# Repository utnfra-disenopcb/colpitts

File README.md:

# Diseño de PCB de oscilador Colpitts de frecuencia variable (80MHz a 100MHz)

## Enunciado
El proyecto consiste en el desarrollo de un oscilador de frecuencia variable, de 80MHz a 100MHz, a través de un capacitor variable (trimmer). El diseño incluye un control automático de amplitud de forma tal de mantener la tensión de salida estable en 1V aproximadamente, sobre una carga de 50Ω y con una THD menor al 5%. Para su construcción se emplea un oscilador tipo Colpitts con configuración base a masa.

## Referencias de diseño

**Tecnologías**
- Mayer (Tecnología 8 mils)
- Pistas: 1.5; 1; 0.75; 0.5; 0.25; 0.20 [mm]
- Vías: 0.8 - Agujero: 0.4 [mm]
- Márgen: 0.25 mm
- Pista más delgada: 0.2 mm
- Dist. a borde: 0.3 mm

**Stack-up**
- FR4 1.6 mm Dual layer
- Componentes en capa superior
- Máscara anti-soldante: Azul
- Sin requerimientos especiales
- Terminación: HASL c/Pb
- Espesor de Cu: 1oz

## Historial de versiones

**Versión 1.0**
- Primera versión.

## Mejoras pendientes v1.1
- Mejora 1
- Mejora 2
- Mejora 3

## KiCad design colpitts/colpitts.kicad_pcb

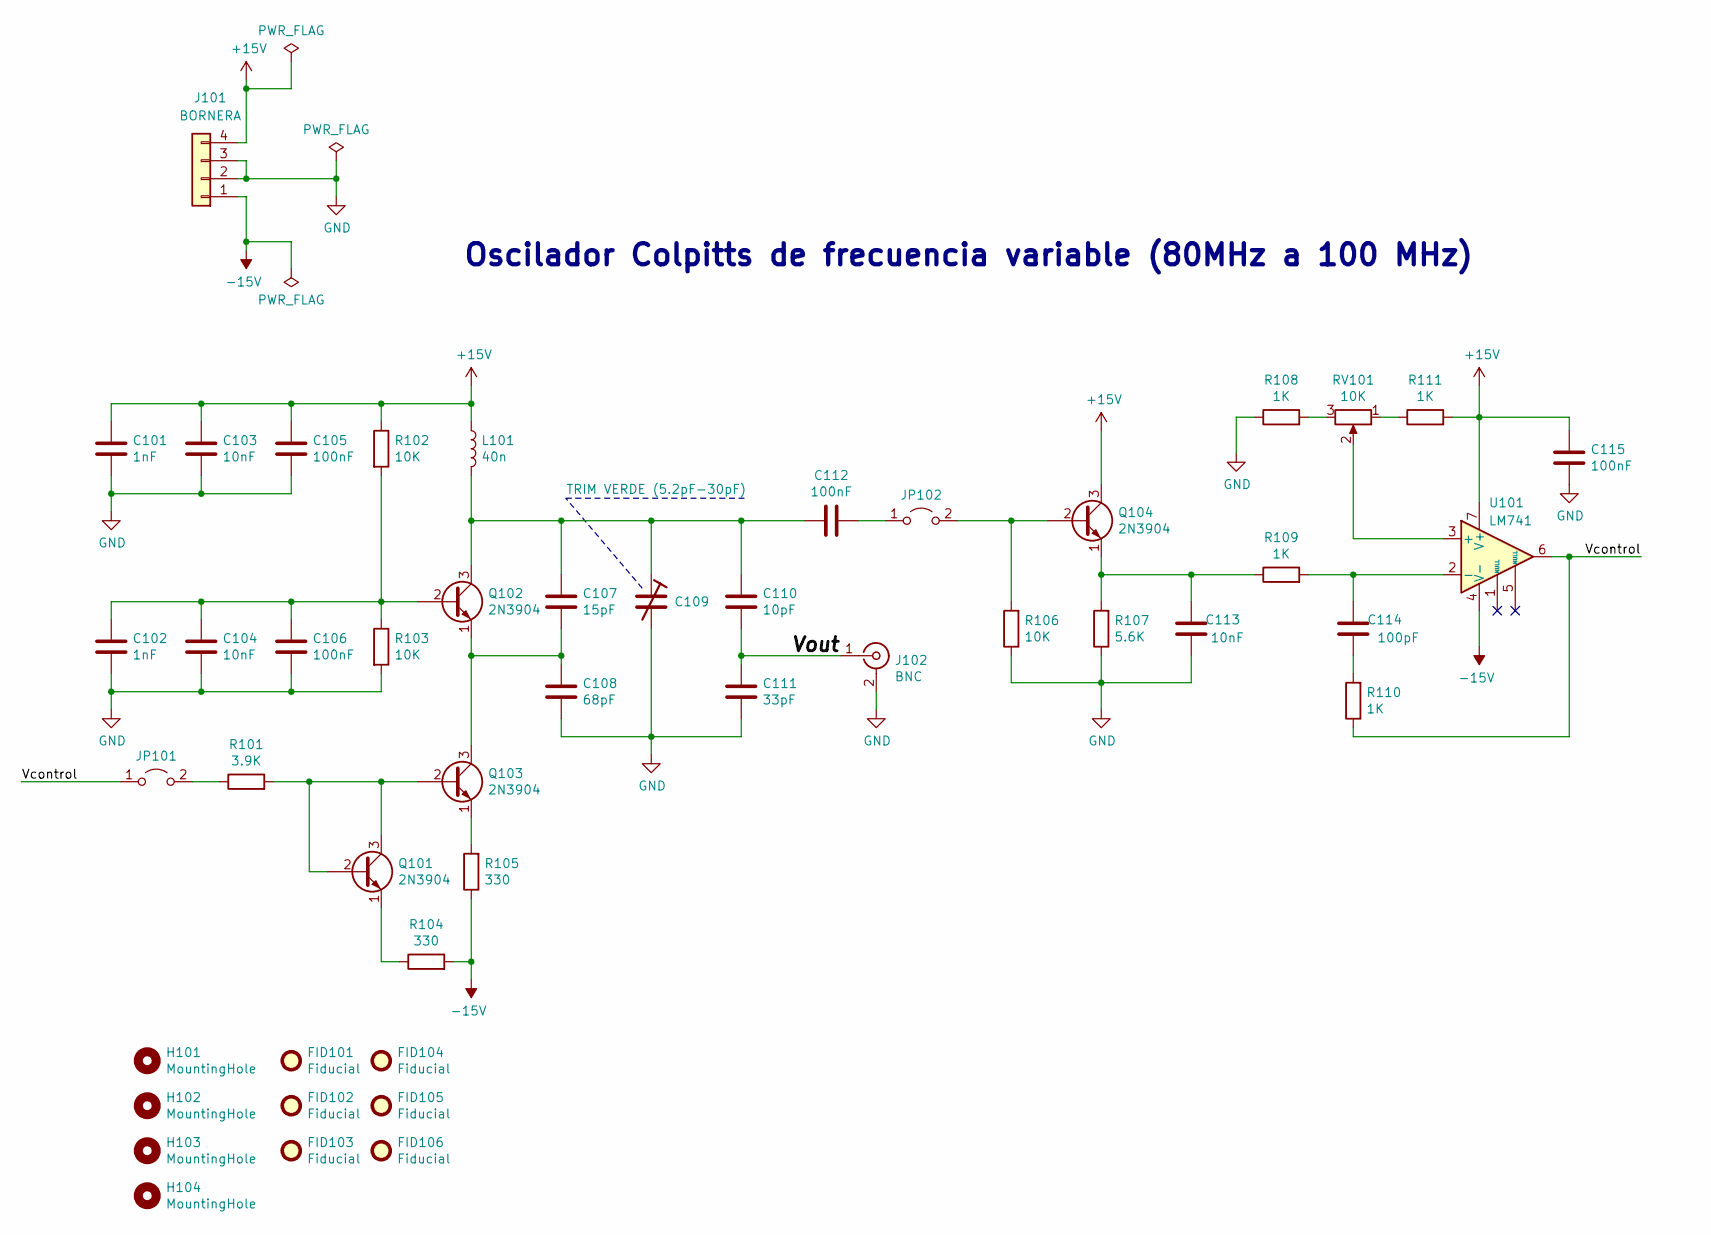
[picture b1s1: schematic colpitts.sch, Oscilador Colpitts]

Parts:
C101, C102: 1nF; C_0805_2012Metric_Pad1.15x1.40mm_HandSolder
C103, C104, C113: 10nF; C_0805_2012Metric_Pad1.15x1.40mm_HandSolder
C105, C106, C112, C115: 100nF; C_0805_2012Metric_Pad1.15x1.40mm_HandSolder
C107: 15pF; C_0805_2012Metric_Pad1.15x1.40mm_HandSolder
C108: 68pF; C_0805_2012Metric_Pad1.15x1.40mm_HandSolder
C109: TRIM VERDE (5.2pF-30pF); Trimmer_Capacitor_Verde; DigiKey PN 490-1960-ND
C110: 10pF; C_0805_2012Metric_Pad1.15x1.40mm_HandSolder
C111: 33pF; C_0805_2012Metric_Pad1.15x1.40mm_HandSolder
C114: 100pF; C_0805_2012Metric_Pad1.15x1.40mm_HandSolder
FID101, FID102, FID103, FID104, FID105, FID106: Fiducial; Fiducial_1mm_Mask2mm
H101, H102, H103, H104: MountingHole; MountingHole_3.2mm_M3_Pad_Via
J101: BORNERA; TerminalBlock_1x04_P5.00mm; DigiKey PN 277-1579-ND
J102: BNC; BNC_Conn_Horizontal; DigiKey PN A32244-ND
JP101, JP102: Jumper_2_Open; PinHeader_1x02_P2.54mm_Vertical
L101: 40n; L_Axial_L5.3mm_D2.2mm_P10.16mm_Horizontal_Vishay_IM-1
Q101, Q102, Q103, Q104: 2N3904; TO-92_Inline; DigiKey PN 2N3904FS-ND
R101: 3.9K; R_0805_2012Metric_Pad1.15x1.40mm_HandSolder
R102, R103, R106: 10K; R_0805_2012Metric_Pad1.15x1.40mm_HandSolder
R104, R105: 330; R_0805_2012Metric_Pad1.15x1.40mm_HandSolder
R107: 5.6K; R_0805_2012Metric_Pad1.15x1.40mm_HandSolder
R108, R109, R110, R111: 1K; R_0805_2012Metric_Pad1.15x1.40mm_HandSolder
RV101: 10K; Preset_Multivuelta
U101: LM741; DIP-8_W10.16mm; DigiKey PN LM741CNNS/NOPB-ND

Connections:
+15V: C101.1, C103.1, C105.1, C115.1, J101.4, L101.1, Q104.3 (C), R102.1, R111.2, U101.7 (V+)
-15V: J101.1, R104.2, R105.1, U101.4 (V-)
/Vcontrol: JP101.1 (A), R110.1, U101.6
/Vout: C110.2, C111.1, J102.1 (In)
GND: C101.2, C102.2, C103.2, C104.2, C105.2, C106.2, C108.2, C109.2, C111.2, C113.1, C115.2, J101.2, J101.3, J102.2 (Ext), R103.2, R106.1, R107.1, R108.1
unnamed: C102.1, C104.1, C106.1, Q102.2 (B), R102.2, R103.1
unnamed: C107.1, C109.1, C110.1, C112.2, L101.2, Q102.3 (C)
unnamed: C107.2, C108.1, Q102.1 (E), Q103.3 (C)
unnamed: C112.1, JP102.1 (A)
unnamed: C113.2, Q104.1 (E), R107.2, R109.1
unnamed: C114.1, R110.2
unnamed: C114.2, R109.2, U101.2 (-)
unnamed: JP101.2 (B), R101.1
unnamed: JP102.2 (B), Q104.2 (B), R106.2
unnamed: Q101.1 (E), R104.1
unnamed: Q101.2 (B), Q101.3 (C), Q103.2 (B), R101.2
unnamed: Q103.1 (E), R105.2
unnamed: R108.2, RV101.3
unnamed: R111.1, RV101.1
unnamed: RV101.2, U101.3 (+)

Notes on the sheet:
Oscilador Colpitts de frecuencia variable (80MHz a 100 MHz)

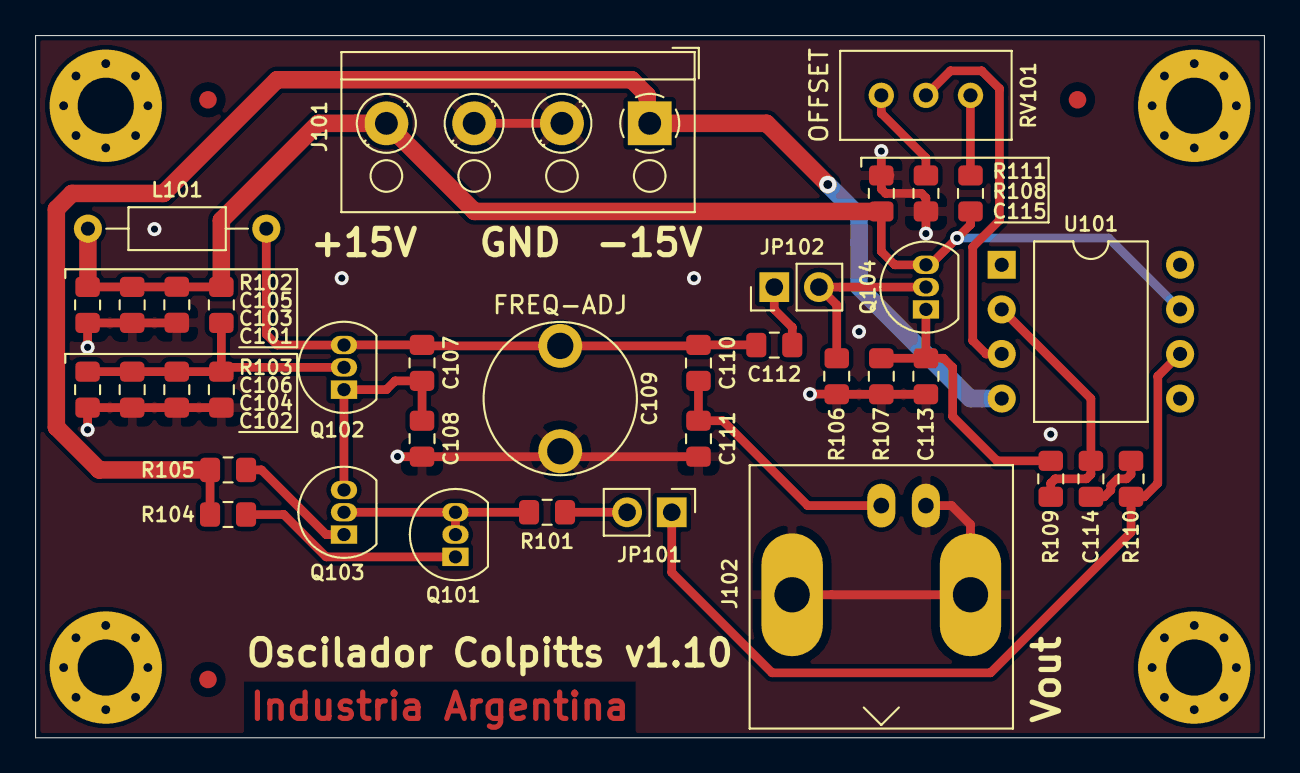
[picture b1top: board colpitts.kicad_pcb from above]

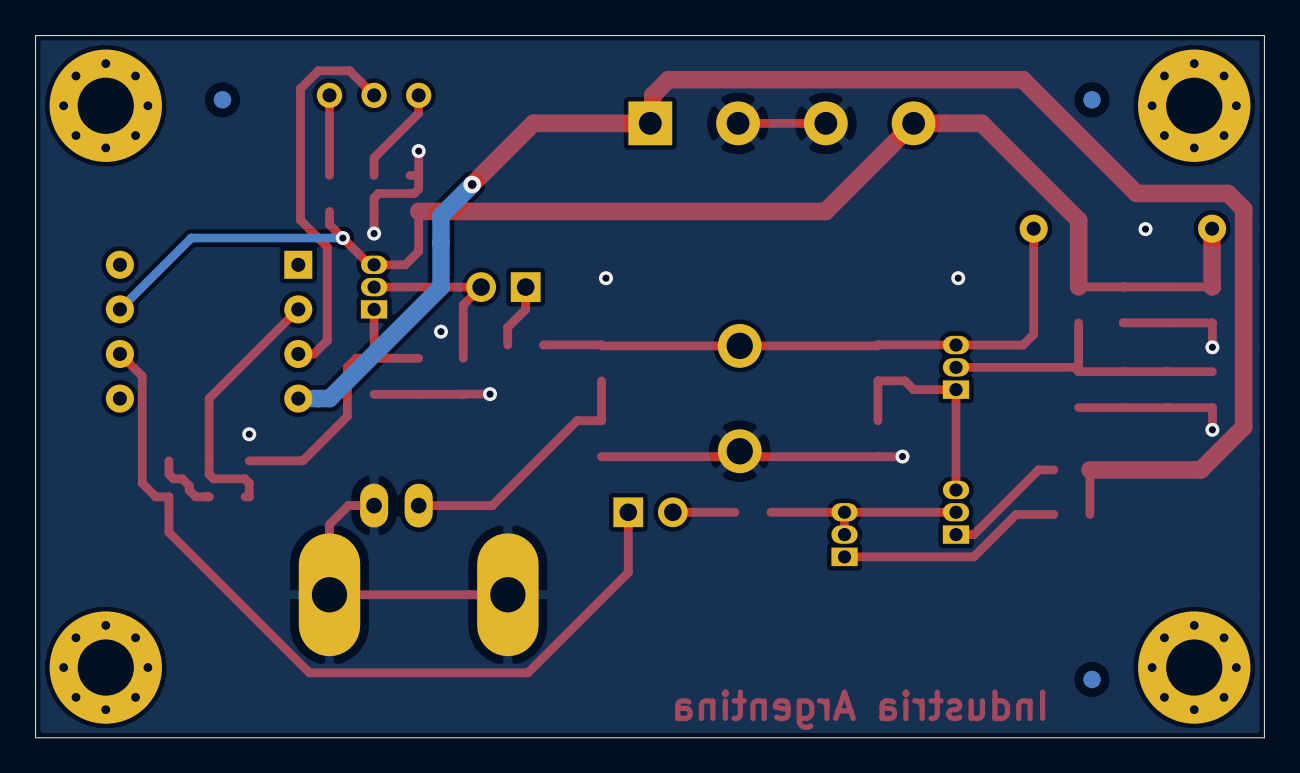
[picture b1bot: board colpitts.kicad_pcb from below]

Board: 2 copper layers, 70.0 x 40.0 mm, 47 parts (3 on the bottom side), 20 nets.

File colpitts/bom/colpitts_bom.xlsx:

Source: | C:\Users\mmoreyra\Downloads\[Desarrollo]\colpitts\colpitts\colpitts.sch
Date: | 43700.720300925925
Tool: | Eeschema (5.1.2)-1
Generator: | C:\Program Files\KiCad\bin\scripting\plugins/bom_csv_grouped_by_value.py
Component Count: | 37
Individual Components:
Item | Qty | Reference(s) | Value | LibPart | Footprint | Datasheet | Description | DigiKey PN | Manf PN
 |  | C101 | 1nF | Device:C | Capacitor_SMD:C_0805_2012Metric_Pad1.15x1.40mm_HandSolder | ~
 |  | C102 | 1nF | Device:C | Capacitor_SMD:C_0805_2012Metric_Pad1.15x1.40mm_HandSolder | ~
 |  | C103 | 10nF | Device:C | Capacitor_SMD:C_0805_2012Metric_Pad1.15x1.40mm_HandSolder | ~
 |  | C104 | 10nF | Device:C | Capacitor_SMD:C_0805_2012Metric_Pad1.15x1.40mm_HandSolder | ~
 |  | C105 | 100nF | Device:C | Capacitor_SMD:C_0805_2012Metric_Pad1.15x1.40mm_HandSolder | ~
 |  | C106 | 100nF | Device:C | Capacitor_SMD:C_0805_2012Metric_Pad1.15x1.40mm_HandSolder | ~
 |  | C107 | 15pF | Device:C | Capacitor_SMD:C_0805_2012Metric_Pad1.15x1.40mm_HandSolder | ~
 |  | C108 | 68pF | Device:C | Capacitor_SMD:C_0805_2012Metric_Pad1.15x1.40mm_HandSolder | ~
 |  | C109 | TRIM VERDE (5.2pF-30pF) | Device:CTRIM | colpitts:Trimmer_Capacitor_Verde | https://media.digikey.com/pdf/Data%20Sheets/Murata%20PDFs/Ce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 | CAP TRIMMER 5.2-30PF 100V TH | 490-1960-ND | TZ03R300E169B00
 |  | C110 | 10pF | Device:C | Capacitor_SMD:C_0805_2012Metric_Pad1.15x1.40mm_HandSolder | ~
 |  | C111 | 33pF | Device:C | Capacitor_SMD:C_0805_2012Metric_Pad1.15x1.40mm_HandSolder | ~
 |  | C112 | 100nF | Device:C | Capacitor_SMD:C_0805_2012Metric_Pad1.15x1.40mm_HandSolder | ~
 |  | C113 | 10nF | Device:C | Capacitor_SMD:C_0805_2012Metric_Pad1.15x1.40mm_HandSolder | ~
 |  | C114 | 100pF | Device:C | Capacitor_SMD:C_0805_2012Metric_Pad1.15x1.40mm_HandSolder | ~
 |  | C115 | 100nF | Device:C | Capacitor_SMD:C_0805_2012Metric_Pad1.15x1.40mm_HandSolder | ~
 |  | J101 | BORNERA | Connector_Generic:Conn_01x04 | colpitts:TerminalBlock_1x04_P5.00mm | https://media.digikey.com/pdf/Data%20Sheets/Phoenix%20Contac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 | TERM BLK 4POS SIDE ENTRY 5MM PCB | 277-1579-ND | 1935187
 |  | J102 | BNC | Connector:Conn_Coaxial | colpitts:BNC_Conn_Horizontal | https://www.te.com/commerce/DocumentDelivery/DDEController?A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 | CONN BNC JACK R/A 50 OHM PCB | A32244-ND | 5227161-1
 |  | JP101 | Jumper_2_Open | Jumper:Jumper_2_Open | Connector_PinHeader_2.54mm:PinHeader_1x02_P2.54mm_Vertical | ~
 |  | JP102 | Jumper_2_Open | Jumper:Jumper_2_Open | Connector_PinHeader_2.54mm:PinHeader_1x02_P2.54mm_Vertical | ~
 |  | L101 | 40n | Device:L | Inductor_THT:L_Axial_L5.3mm_D2.2mm_P10.16mm_Horizontal_Vishay_IM-1 | ~
 |  | Q101 | 2N3904 | Transistor_BJT:2N3904 | Package_TO_SOT_THT:TO-92_Inline | https://www.onsemi.com/pub/Collateral/PZT3904-D.pdf | TRANS NPN 40V 0.2A TO-92 | 2N3904FS-ND | 2N3904BU
 |  | Q102 | 2N3904 | Transistor_BJT:2N3904 | Package_TO_SOT_THT:TO-92_Inline | https://www.onsemi.com/pub/Collateral/PZT3904-D.pdf | TRANS NPN 40V 0.2A TO-92 | 2N3904FS-ND | 2N3904BU
 |  | Q103 | 2N3904 | Transistor_BJT:2N3904 | Package_TO_SOT_THT:TO-92_Inline | https://www.onsemi.com/pub/Collateral/PZT3904-D.pdf | TRANS NPN 40V 0.2A TO-92 | 2N3904FS-ND | 2N3904BU
 |  | Q104 | 2N3904 | Transistor_BJT:2N3904 | Package_TO_SOT_THT:TO-92_Inline | https://www.onsemi.com/pub/Collateral/PZT3904-D.pdf | TRANS NPN 40V 0.2A TO-92 | 2N3904FS-ND | 2N3904BU
 |  | R101 | 3.9K | Device:R | Resistor_SMD:R_0805_2012Metric_Pad1.15x1.40mm_HandSolder | ~
 |  | R102 | 10K | Device:R | Resistor_SMD:R_0805_2012Metric_Pad1.15x1.40mm_HandSolder | ~
 |  | R103 | 10K | Device:R | Resistor_SMD:R_0805_2012Metric_Pad1.15x1.40mm_HandSolder | ~
 |  | R104 | 330 | Device:R | Resistor_SMD:R_0805_2012Metric_Pad1.15x1.40mm_HandSolder | ~
 |  | R105 | 330 | Device:R | Resistor_SMD:R_0805_2012Metric_Pad1.15x1.40mm_HandSolder | ~
 |  | R106 | 10K | Device:R | Resistor_SMD:R_0805_2012Metric_Pad1.15x1.40mm_HandSolder | ~
 |  | R107 | 5.6K | Device:R | Resistor_SMD:R_0805_2012Metric_Pad1.15x1.40mm_HandSolder | ~
 |  | R108 | 1K | Device:R | Resistor_SMD:R_0805_2012Metric_Pad1.15x1.40mm_HandSolder | ~
 |  | R109 | 1K | Device:R | Resistor_SMD:R_0805_2012Metric_Pad1.15x1.40mm_HandSolder | ~
 |  | R110 | 1K | Device:R | Resistor_SMD:R_0805_2012Metric_Pad1.15x1.40mm_HandSolder | ~
 |  | R111 | 1K | Device:R | Resistor_SMD:R_0805_2012Metric_Pad1.15x1.40mm_HandSolder | ~
 |  | RV101 | 10K | Device:R_POT | colpitts:Preset_Multivuelta | ~
 |  | U101 | LM741 | Amplifier_Operational:LM741 | Package_DIP:DIP-8_W10.16mm | http://www.ti.com/lit/ds/symlink/lm741.pdf | IC OPAMP GP 1 CIRCUIT 8DIP | LM741CNNS/NOPB-ND | LM741CN/NOPB
Collated Components:
Item | Qty | Reference(s) | Value | LibPart | Footprint | Datasheet | Description | DigiKey PN | Manf PN
1 | 2 | C101, C102 | 1nF | Device:C | Capacitor_SMD:C_0805_2012Metric_Pad1.15x1.40mm_HandSolder | ~
2 | 3 | C103, C104, C113 | 10nF | Device:C | Capacitor_SMD:C_0805_2012Metric_Pad1.15x1.40mm_HandSolder | ~
3 | 4 | C105, C106, C112, C115 | 100nF | Device:C | Capacitor_SMD:C_0805_2012Metric_Pad1.15x1.40mm_HandSolder | ~
4 | 1 | C107 | 15pF | Device:C | Capacitor_SMD:C_0805_2012Metric_Pad1.15x1.40mm_HandSolder | ~
5 | 1 | C108 | 68pF | Device:C | Capacitor_SMD:C_0805_2012Metric_Pad1.15x1.40mm_HandSolder | ~
6 | 1 | C109 | TRIM VERDE (5.2pF-30pF) | Device:CTRIM | colpitts:Trimmer_Capacitor_Verde | https://media.digikey.com/pdf/Data%20Sheets/Murata%20PDFs/Ce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 | CAP TRIMMER 5.2-30PF 100V TH | 490-1960-ND | TZ03R300E169B00
7 | 1 | C110 | 10pF | Device:C | Capacitor_SMD:C_0805_2012Metric_Pad1.15x1.40mm_HandSolder | ~
8 | 1 | C111 | 33pF | Device:C | Capacitor_SMD:C_0805_2012Metric_Pad1.15x1.40mm_HandSolder | ~
9 | 1 | C114 | 100pF | Device:C | Capacitor_SMD:C_0805_2012Metric_Pad1.15x1.40mm_HandSolder | ~
10 | 1 | J101 | BORNERA | Connector_Generic:Conn_01x04 | colpitts:TerminalBlock_1x04_P5.00mm | https://media.digikey.com/pdf/Data%20Sheets/Phoenix%20Contac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 | TERM BLK 4POS SIDE ENTRY 5MM PCB | 277-1579-ND | 1935187
11 | 1 | J102 | BNC | Connector:Conn_Coaxial | colpitts:BNC_Conn_Horizontal | https://www.te.com/commerce/DocumentDelivery/DDEController?A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 | CONN BNC JACK R/A 50 OHM PCB | A32244-ND | 5227161-1
12 | 2 | JP101, JP102 | Jumper_2_Open | Jumper:Jumper_2_Open | Connector_PinHeader_2.54mm:PinHeader_1x02_P2.54mm_Vertical | ~
13 | 1 | L101 | 40n | Device:L | Inductor_THT:L_Axial_L5.3mm_D2.2mm_P10.16mm_Horizontal_Vishay_IM-1 | ~
14 | 4 | Q101, Q102, Q103, Q104 | 2N3904 | Transistor_BJT:2N3904 | Package_TO_SOT_THT:TO-92_Inline | https://www.onsemi.com/pub/Collateral/PZT3904-D.pdf | TRANS NPN 40V 0.2A TO-92 | 2N3904FS-ND | 2N3904BU
15 | 1 | R101 | 3.9K | Device:R | Resistor_SMD:R_0805_2012Metric_Pad1.15x1.40mm_HandSolder | ~
16 | 3 | R102, R103, R106 | 10K | Device:R | Resistor_SMD:R_0805_2012Metric_Pad1.15x1.40mm_HandSolder | ~
17 | 2 | R104, R105 | 330 | Device:R | Resistor_SMD:R_0805_2012Metric_Pad1.15x1.40mm_HandSolder | ~
18 | 1 | R107 | 5.6K | Device:R | Resistor_SMD:R_0805_2012Metric_Pad1.15x1.40mm_HandSolder | ~
19 | 4 | R108, R109, R110, R111 | 1K | Device:R | Resistor_SMD:R_0805_2012Metric_Pad1.15x1.40mm_HandSolder | ~
20 | 1 | RV101 | 10K | Device:R_POT | colpitts:Preset_Multivuelta | ~
21 | 1 | U101 | LM741 | Amplifier_Operational:LM741 | Package_DIP:DIP-8_W10.16mm | http://www.ti.com/lit/ds/symlink/lm741.pdf | IC OPAMP GP 1 CIRCUIT 8DIP | LM741CNNS/NOPB-ND | LM741CN/NOPB

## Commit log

2019-05-29 Update files
2019-05-29 Inicio proyecto
2019-05-29 Diseño esquemático
2019-05-30 Update diseño esquemático
2019-05-31 Update diseño esquemático (previa anotación componentes)
2019-05-31 Update diseño esquemático (anotación de componentes)
2019-05-31 ERC - Corrección de errores
    1. POWER FLAGS de alimentación.
2019-08-22 Update diseño esquemático (previa asignación de huellas)
2019-08-23 Update diseño esquemático (asignación de huellas y modelos 3d)
2019-08-23 Fin diseño esquemático (bom generada)
2019-08-23 Inicio diseño PCB
2019-08-30 Lectura de netlist, def área pcb, board setup
2019-08-30 Pos componentes, ruteo, rellenos
2019-08-30 Terminación rellenos
2019-08-31 Anotación ref user, DRC, validación serigrafía
2019-08-31 Generación de archivos de fabricación, fin del diseño
